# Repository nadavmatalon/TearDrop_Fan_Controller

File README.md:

#TearDrop Fan Controller

##Table of Contents

* [Screenshots](#screenshots)
* [About the Project](#about-the-project)
* [About the Fan Controller](#about-the-fan-controller)
* [License](#license)

##Screenshots

<table>
	<tr>
		<td align="center" width=25% >
			
		</td>
		<td align="center" width=25% >
			
		</td>
		<td align="center" width=25% >
			
		</td>
		<td align="center" width=25% >
			
		</td>
	</tr>
</table>

##About the Project
 
__TearDrop__ is a custom, open-frame, water-cooled scratch build I’ve been 
working on as part of the SnowCrash initiative.

The __SnowCrash__ initiative aims at designing and building end-to-end customized 
personal computers, addressing unique functional requirements – from developing 
the software control applications, to hardware configuration and case modding. 
As part of the initiative's research phase, the TearDrop customized computer 
prototype has been developed.

The underlying motivation for this specifc project was to research, design, 
prototype and finally create everything that's needed for a fully-customized 
desktop computer.

In this context, I’ve learned to program micro-controllers, design, prototype 
and build electronic circuit boards, make CNC cutting templates, interface with 
various kinds of hardware, write front-end applications, and lots more.

This project also helped me to become proficient in multiple software tools, including: 
[Google Sketchup](http://www.sketchup.com/), 
[Arduino IDE](http://www.arduino.cc/), [Processing 2.0](http://processing.org/), 
[CadSoft Eagle](http://www.cadsoftusa.com/download-eagle/freeware/), 
and [Inkscape](http://www.inkscape.org/en/).
 
The __project-log__ of this build (which I haven't had time to update recently, but 
does include loads of cool pictures :-), can be found 
at [bit-tech](http://forums.bit-tech.net/showthread.php?t=234218).

##About the Fan Controller

This repo contains the custom Fan Controller I’ve designed and built 
to control __TearDrop__’s cooling fans.

This repo contains the following files:

* __arduino__

    The source code for the 2 x ATmega328P that run the Fan Controller 

    The files can can be directly accessed by clicking these links:

    * [Fan Controller: IC1](arduino/TearDrop_Fan_Controller_IC1/TearDrop_Fan_Controller_IC1.ino)

    * [Fan Controller: IC2](arduino/TearDrop_Fan_Controller_IC2/TearDrop_Fan_Controller_IC2.ino)

	The source code requires three supporting open-source [Arduino](http://www.arduino.cc/) libraries.

	For convenience, these libraries are inlcuded here in their own sub-folder.

	Credit goes to:

	[PinChangeInt](http://playground.arduino.cc/Main/PinChangeInt)

	[OneWire](https://github.com/ntruchsess/arduino-OneWire/tree/master)

	[WSWire](https://github.com/steamfire/WSWireLib)

* __eagle__

    This folder contains the complete hardware schematics & PCB design of the Fan Controller.

    __Please do not click on the files in this sub-folder as they are in foramts that 
    are incompatible with Github's hosting server__.

    However, the files can be downloaded and run as usual with [CadSoft](http://www.cadsoftusa.com/?language=en)'s 
    free version of [Eagle](http://www.cadsoftusa.com/download-eagle/freeware/).

* __parts__

	A speadsheet with all information about the parts used for building the Fan Controller.

	__The file in this sub-folder is also in a foramt that's incompatible with Github's hosting server__.

    However, it can be downloaded and run as usual with any spreadsheet editing software.

##  License

<p>Released under the <a href="http://www.opensource.org/licenses/MIT">MIT license</a>.</p>

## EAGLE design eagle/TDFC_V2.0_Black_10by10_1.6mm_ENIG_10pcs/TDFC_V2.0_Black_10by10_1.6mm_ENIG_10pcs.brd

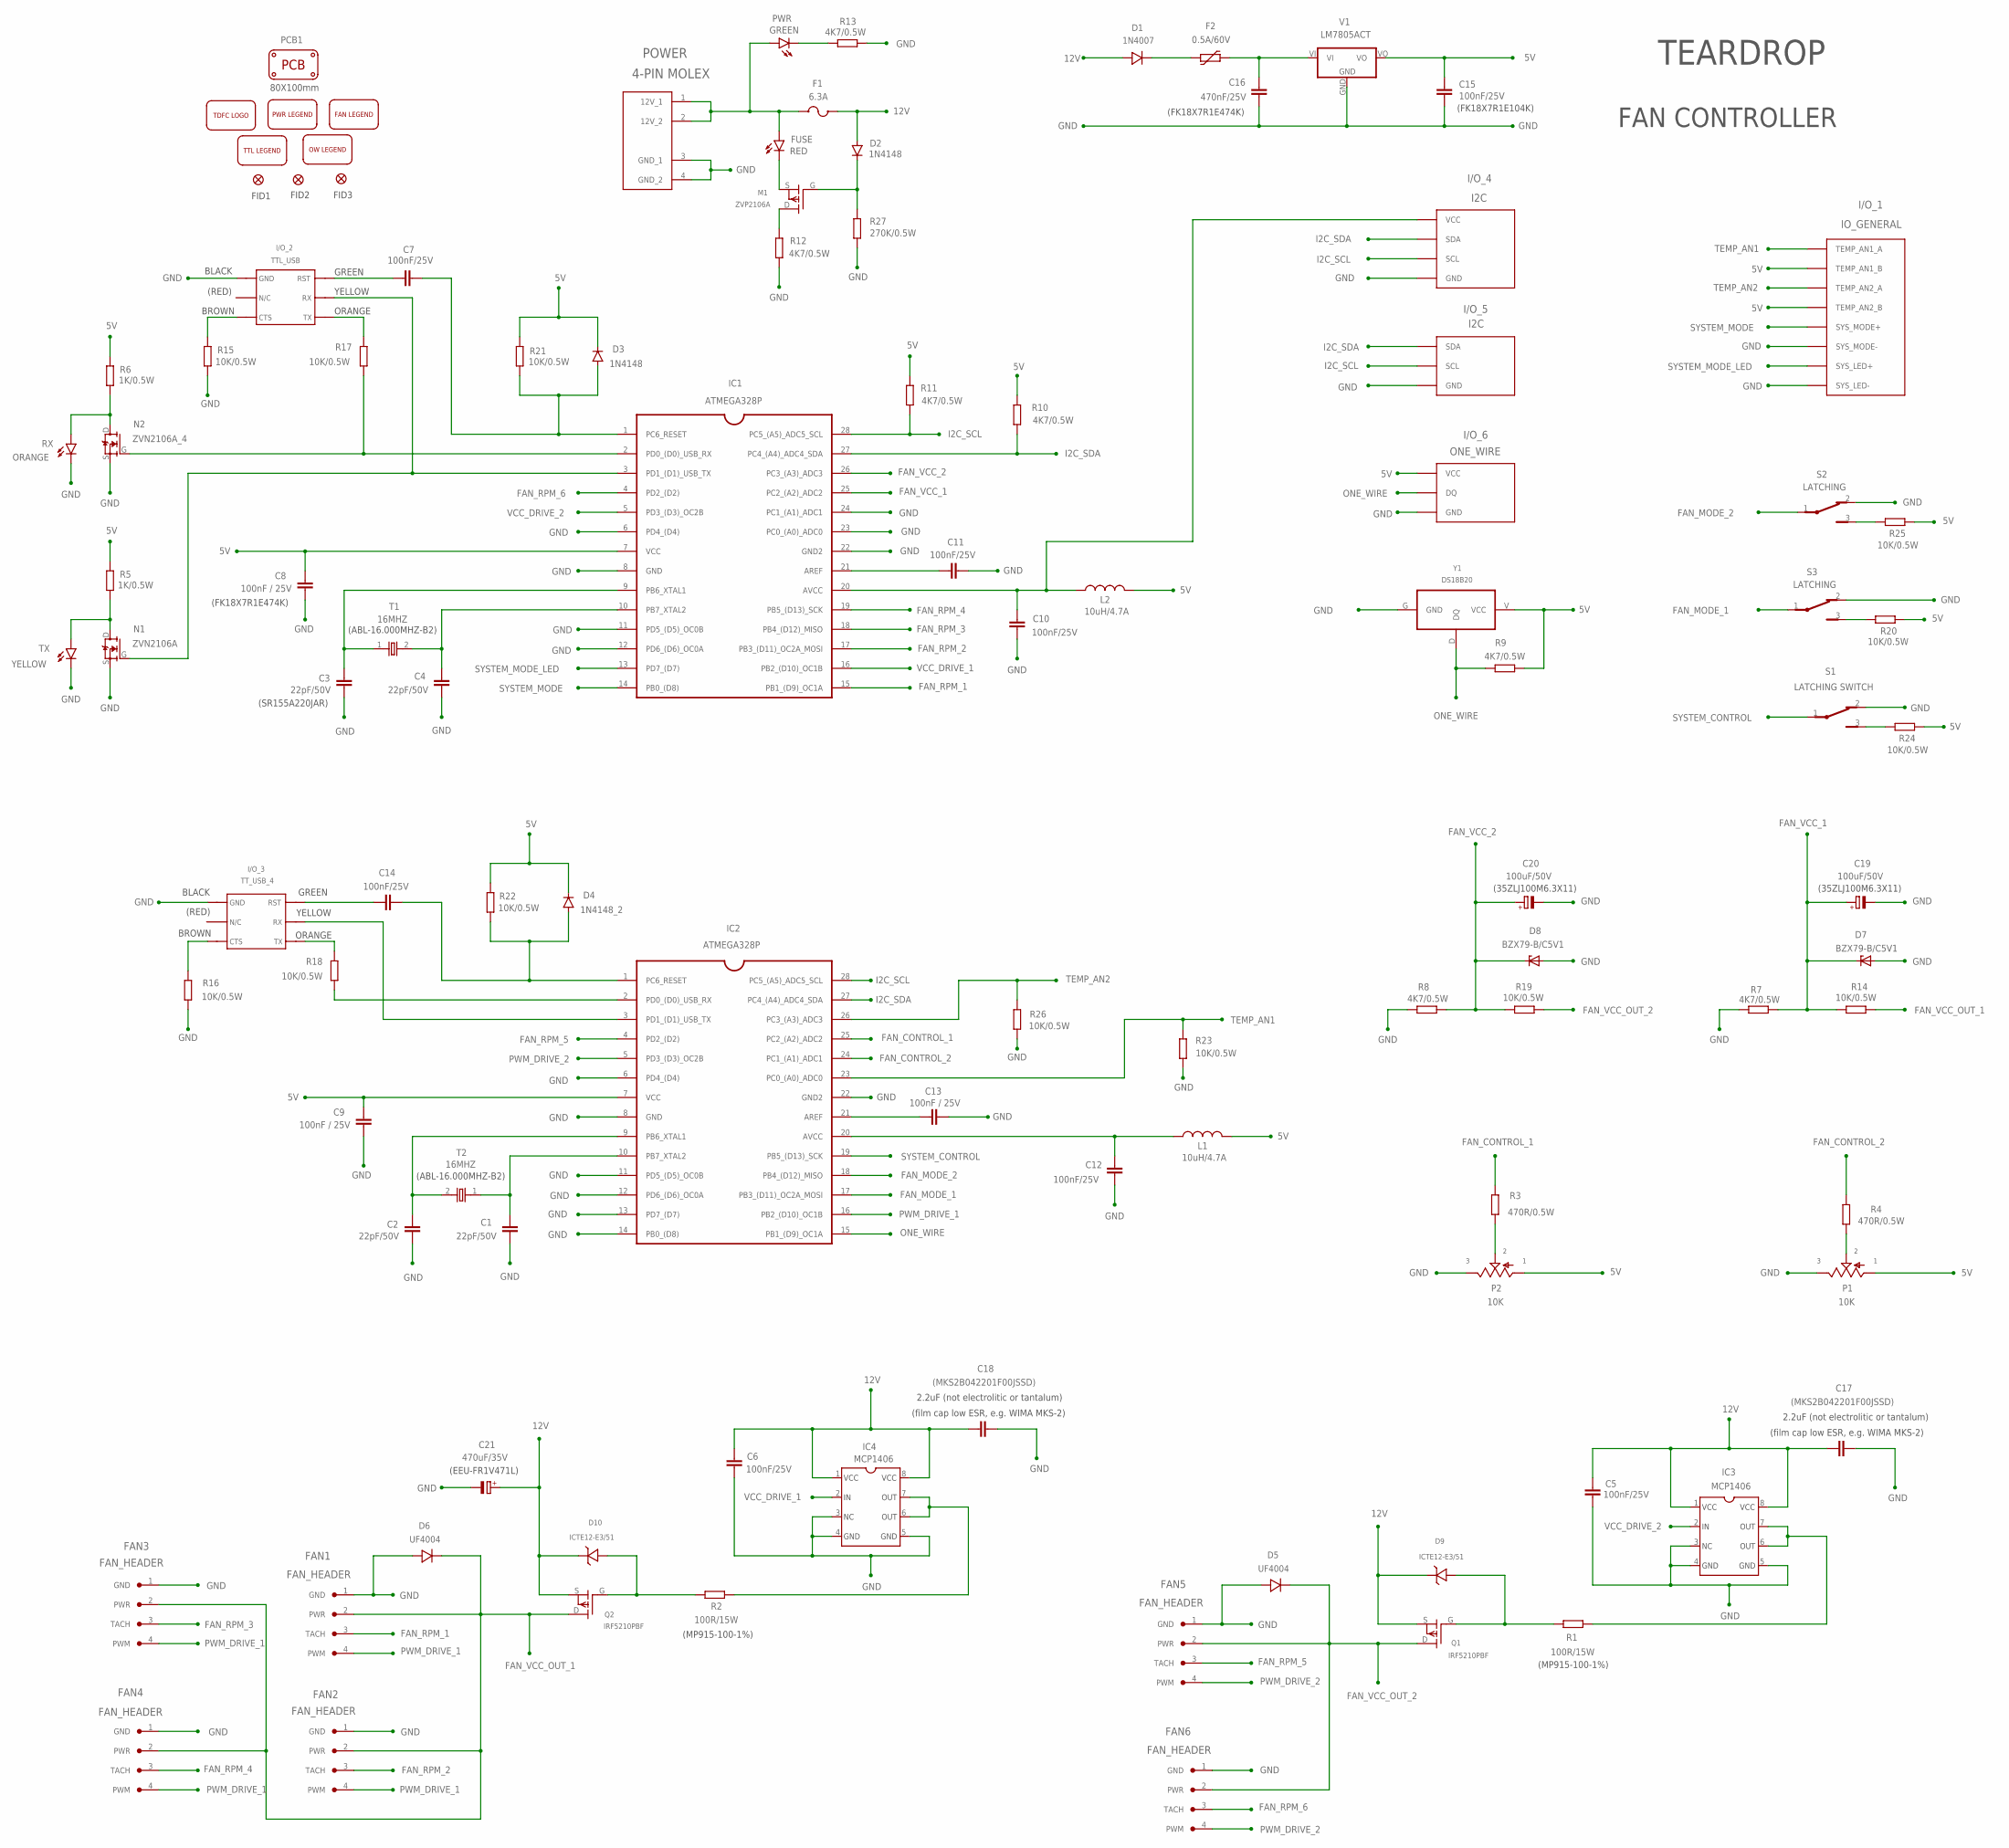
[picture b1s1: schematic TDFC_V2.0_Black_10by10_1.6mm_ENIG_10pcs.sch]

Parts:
C1, C2: 22pF/50V; MLCC_CERAMIC_9
C3, C4: 22pF/50V; MLCC_CERAMIC_11
C5, C6: 100nF/25V; MLCC_CERAMIC_5
C7: 100nF/25V; MLCC_CERAMIC_7
C8, C9: 100nF / 25V; MLCC_CERAMIC_5
C10: 100nF/25V; MLCC_CERAMIC
C11: 100nF/25V; MLCC_CERAMIC_17
C12: 100nF/25V; MLCC_CERAMIC_6
C13: 100nF / 25V; MLCC_CERAMIC_6
C14: 100nF/25V; MLCC_CERAMIC_14
C15: 100nF/25V; MLCC_CERAMIC_16
C16: 470nF/25V; MLCC_CERAMIC_15
C17, C18: (MKS2B042201F00JSSD); WIMA_CAPACITOR_2
C19, C20: 100uF/50V; CAPACITOR_6.3_RIGHT
C21: 470uF/35V; ELECTROLYTIC_CAPACITOR_RIGHT
D1: 1N4007; UF4004
D2, D3: 1N4148
D4: 1N4148_2
D5, D6: UF4004; UF4004_2
D7: BZX79-B/C5V1; DO34_2
D8: BZX79-B/C5V1; DO34Z7
D9, D10: ICTE12-E3/51; TVS_DIODE_5
F1: 6.3A; FUSE_GLASS
F2: 0.5A/60V; PTC
FAN1, FAN2, FAN3, FAN4, FAN5, FAN6: FAN_HEADER; 4PIN_FAN_HEADER
FID1, FID2, FID3: FIDUCIAL1X2; FIDUCIAL-1X2
FUSE: RED; LED_1.8_LEFT
I/O_1: IO_GENERAL; IO_GENERAL_7
I/O_2: TTL_USB; TTL_USB_5
I/O_3: TT_USB_4
I/O_4: I2C; 4_PIN_HEADER_VERTICAL_2
I/O_5: I2C; 3_PIN_VERTICAL_4
I/O_6: ONE_WIRE; 3_PIN_VERTICAL
IC1: ATMEGA328P
IC2: ATMEGA328P; ATMEGA328P_2
IC3, IC4: MCP1406; TC4420
L1, L2: 10uH/4.7A; INDUCTOR
M1: ZVP2106A
N1: ZVN2106A
N2: ZVN2106A_4
P1, P2: 10K; POTENTIMETER_SQUARE
PCB1: 80X100mm; DP10080_V1
POWER: 4-PIN MOLEX; MOLEX_4PIN_2
PWR: GREEN; LED_1.8_LEFT
Q1, Q2: IRF5210PBF; IRF5210
R1, R2: 100R/15W; V234/12
R3, R4: 470R/0.5W; 0204/5
R5, R6: 1K/0.5W; 0204/5
R7, R8, R9, R10, R11, R12, R13: 4K7/0.5W; 0204/5
R14, R15, R16, R17, R18, R19, R20, R21, R22, R23, R24, R25, R26: 10K/0.5W; 0204/5
R27: 270K/0.5W; 0204/5
RX: ORANGE; LED_1.8_LEFT_2
S1: LATCHING SWITCH; SLIDING_SWITCH_4
S2, S3: LATCHING; SLIDING_SWITCH_5
T1, T2: 16MHZ; CRYSTAL_16MHZ
TX: YELLOW; LED_1.8_LEFT_2
U$1: TDFC_LOGO
U$2: MOLEX_4PIN_LEGEND_2
U$3: FAN_HEADER_LEGEND
U$4: TTL_USB_6
U$5: 3_PIN_VERTICAL_LEGEND
V1: LM7805ACT; LM7805
Y1: DS18B20

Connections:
1: C10.1, I/O_4.VCC, IC1.20 (AVCC), L2.1
5V: C8.1, C9.1, C15.2, D3.C, D4.C, I/O_1.TEMP_AN1_B, I/O_1.TEMP_AN2_B, I/O_6.VCC, IC1.7 (VCC), IC2.7 (VCC), L1.2, L2.2, P1.1 (A), P2.1 (A), R5.2, R6.2, R9.2, R10.1, R11.1, R20.1, R21.2, R22.2, R24.2, R25.2, V1.VO, Y1.V (VCC)
12V: C5.2, C6.2, C17.1, C18.1, C21.+, D1.A, D2.A, D9.C, D10.C, F1.2, IC3.1, IC3.8, IC4.1, IC4.8, Q1.S, Q2.S
FAN_CONTROL_1: IC2.25 (PC2_(A2)_ADC2), R3.1
FAN_CONTROL_2: IC2.24 (PC1_(A1)_ADC1), R4.1
FAN_MODE_1: IC2.17 (PB3_(D11)_OC2A_MOSI), S3.1
FAN_MODE_2: IC2.18 (PB4_(D12)_MISO), S2.1
FAN_RPM_1: FAN1.3 (TACH), IC1.15 (PB1_(D9)_OC1A)
FAN_RPM_2: FAN2.3 (TACH), IC1.17 (PB3_(D11)_OC2A_MOSI)
FAN_RPM_3: FAN3.3 (TACH), IC1.18 (PB4_(D12)_MISO)
FAN_RPM_4: FAN4.3 (TACH), IC1.19 (PB5_(D13)_SCK)
FAN_RPM_5: FAN5.3 (TACH), IC2.4 (PD2_(D2))
FAN_RPM_6: FAN6.3 (TACH), IC1.4 (PD2_(D2))
FAN_VCC_1: C19.+, D7.C, IC1.25 (PC2_(A2)_ADC2), R7.1, R14.2
FAN_VCC_2: C20.+, D8.C, IC1.26 (PC3_(A3)_ADC3), R8.1, R19.2
FAN_VCC_OUT_1: D6.C, FAN1.2 (PWR), FAN2.2 (PWR), FAN3.2 (PWR), FAN4.2 (PWR), Q2.D, R14.1
FAN_VCC_OUT_2: D5.C, FAN5.2 (PWR), FAN6.2 (PWR), Q1.D, R19.1
GND: C1.2, C2.2, C3.2, C4.2, C5.1, C6.1, C8.2, C9.2, C10.2, C11.2, C12.2, C13.2, C15.1, C16.2, C17.2, C18.2, C19.-, C20.-, C21.-, D5.A, D6.A, D7.A, D8.A, FAN1.1 (GND), FAN2.1 (GND), FAN3.1 (GND), FAN4.1 (GND), FAN5.1 (GND), FAN6.1 (GND), I/O_1.SYSTEM_LED- (SYS_LED-), I/O_1.SYSTEM_MODE- (SYS_MODE-), I/O_2.GND, I/O_3.GND, I/O_4.GND, I/O_5.GND, I/O_6.GND, IC1.6 (PD4_(D4)), IC1.8 (GND), IC1.11 (PD5_(D5)_OC0B), IC1.12 (PD6_(D6)_OC0A), IC1.22 (GND2), IC1.23 (PC0_(A0)_ADC0), IC1.24 (PC1_(A1)_ADC1), IC2.6 (PD4_(D4)), IC2.8 (GND), IC2.11 (PD5_(D5)_OC0B), IC2.12 (PD6_(D6)_OC0A), IC2.13 (PD7_(D7)), IC2.14 (PB0_(D8)), IC2.22 (GND2), IC3.3, IC3.4, IC3.5, IC4.3, IC4.4, IC4.5, N1.S, N2.S, P1.3 (E), P2.3 (E), POWER.3 (GND_1), POWER.4 (GND_2), R7.2, R8.2, R12.1, R13.1, R15.1, R16.2, R23.2, R26.2, R27.2, RX.K (C), S1.2, S2.2, S3.2, TX.K (C), V1.GND, Y1.G (GND)
I2C_SCL: I/O_4.SCL, I/O_5.SCL, IC1.28 (PC5_(A5)_ADC5_SCL), IC2.28 (PC5_(A5)_ADC5_SCL), R11.2
I2C_SDA: I/O_4.SDA, I/O_5.SDA, IC1.27 (PC4_(A4)_ADC4_SDA), IC2.27 (PC4_(A4)_ADC4_SDA), R10.2
unnamed: C14.1, I/O_3.RST
unnamed: D2.C, M1.G, R27.1
unnamed: C13.1, IC2.21 (AREF)
unnamed: F1.1, FUSE.A, POWER.1 (12V_1), POWER.2 (12V_2), PWR.A
unnamed: PWR.K (C), R13.2
unnamed: I/O_3.RX, IC2.3 (PD1_(D1)_USB_TX)
unnamed: IC3.6, IC3.7, R1.2
unnamed: D10.A, Q2.G, R2.1
unnamed: IC4.6, IC4.7, R2.2
unnamed: FUSE.K (C), M1.S
unnamed: I/O_3.TX, R18.1
unnamed: C11.1, IC1.21 (AREF)
unnamed: D9.A, Q1.G, R1.1
unnamed: I/O_3.CTS, R16.1
unnamed: D1.C, F2.1
unnamed: N1.D, R5.1, TX.A
unnamed: N2.D, R6.1, RX.A
unnamed: M1.D, R12.2
unnamed: R25.1, S2.3
unnamed: C12.1, IC2.20 (AVCC), L1.1
unnamed: R20.2, S3.3
unnamed: IC2.2 (PD0_(D0)_USB_RX), R18.2
unnamed: R24.1, S1.3
unnamed: P2.2 (S), R3.2
unnamed: C4.1, IC1.10 (PB7_XTAL2), T1.2
unnamed: C14.2, D4.A, IC2.1 (PC6_RESET), R22.1
unnamed: C3.1, IC1.9 (PB6_XTAL1), T1.1
unnamed: P1.2 (S), R4.2
unnamed: C2.1, IC2.9 (PB6_XTAL1), T2.2
unnamed: C1.1, IC2.10 (PB7_XTAL2), T2.1
ONE_WIRE: I/O_6.DQ, IC2.15 (PB1_(D9)_OC1A), R9.1, Y1.D (DQ)
POST_FUSE: C16.1, F2.2, V1.VI
PWM_DRIVE_1: FAN1.4 (PWM), FAN2.4 (PWM), FAN3.4 (PWM), FAN4.4 (PWM), IC2.16 (PB2_(D10)_OC1B)
PWM_DRIVE_2: FAN5.4 (PWM), FAN6.4 (PWM), IC2.5 (PD3_(D3)_OC2B)
RESET: C7.1, D3.A, IC1.1 (PC6_RESET), R21.1
SYSTEM_CONTROL: IC2.19 (PB5_(D13)_SCK), S1.1
SYSTEM_MODE: I/O_1.SYSTEM_MODE+ (SYS_MODE+), IC1.14 (PB0_(D8))
SYSTEM_MODE_LED: I/O_1.SYSTEM_LED+ (SYS_LED+), IC1.13 (PD7_(D7))
TEMP_AN1: I/O_1.TEMP_AN1_A, IC2.23 (PC0_(A0)_ADC0), R23.1
TEMP_AN2: I/O_1.TEMP_AN2_A, IC2.26 (PC3_(A3)_ADC3), R26.1
USB_CTS: I/O_2.CTS, R15.2
USB_RESET_2: C7.2, I/O_2.RST
USB_RX: IC1.2 (PD0_(D0)_USB_RX), N2.G, R17.2
USB_RX_2: I/O_2.TX, R17.1
USB_TX: I/O_2.RX, IC1.3 (PD1_(D1)_USB_TX), N1.G
VCC_DRIVE_1: IC1.16 (PB2_(D10)_OC1B), IC4.2
VCC_DRIVE_2: IC1.5 (PD3_(D3)_OC2B), IC3.2

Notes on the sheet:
FID1
FID2
FID3
(film cap low ESR, e.g. WIMA MKS-2)
TEARDROP
GREEN
YELLOW
ORANGE
BROWN
BLACK
(RED)
2.2uF (not electrolitic or tantalum)
(FK18X7R1E104K)
(FK18X7R1E474K)
(SR155A220JAR)
(EEU-FR1V471L)
(35ZLJ100M6.3X11)
(MP915-100-1%)
FAN CONTROLLER
(ABL-16.000MHZ-B2)

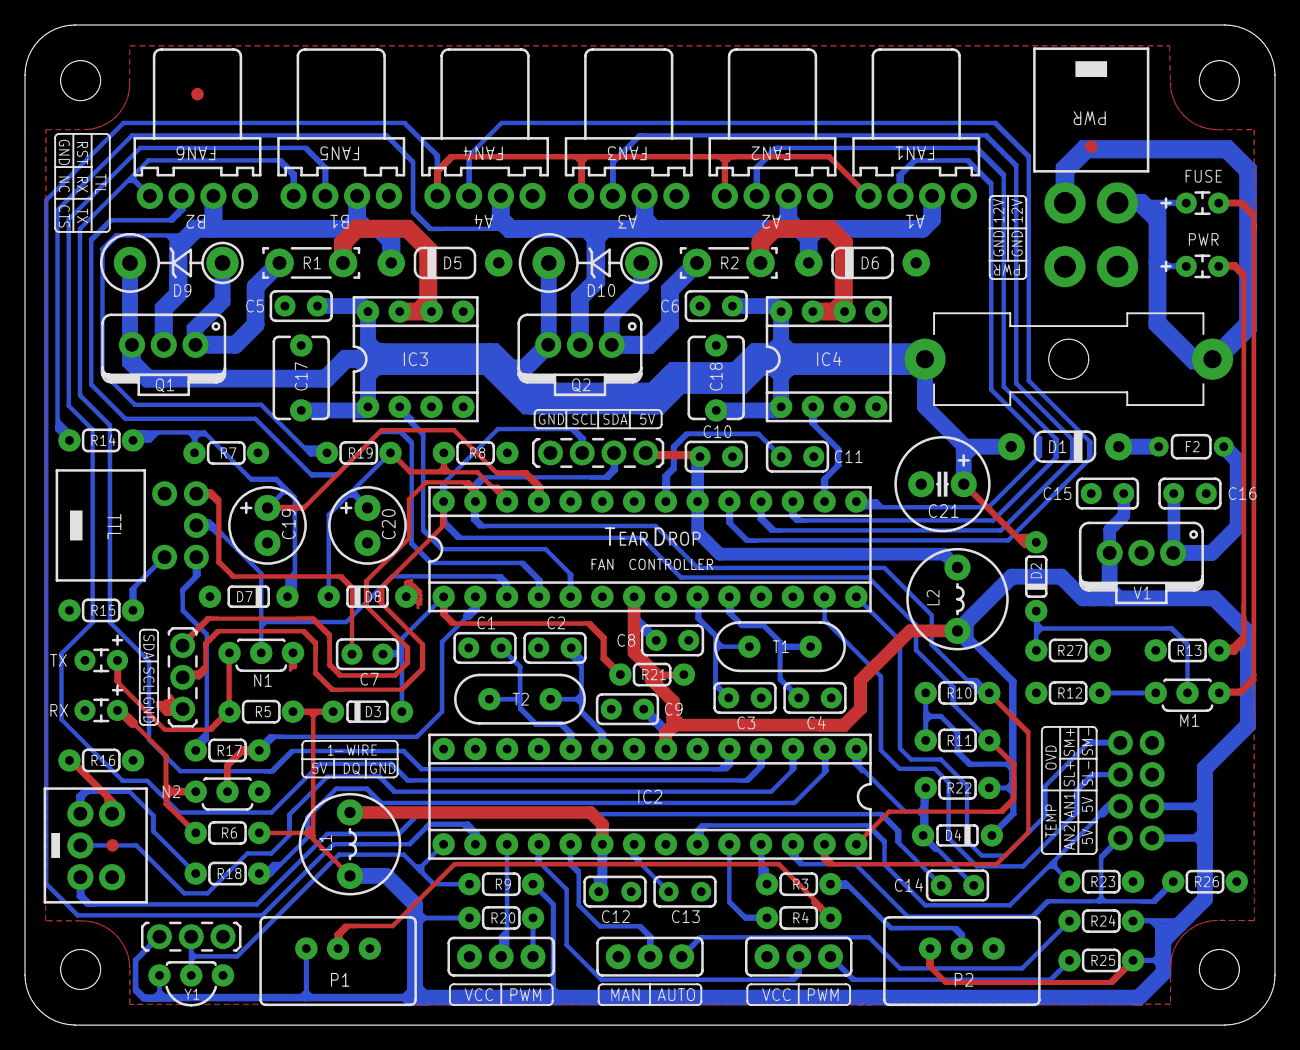
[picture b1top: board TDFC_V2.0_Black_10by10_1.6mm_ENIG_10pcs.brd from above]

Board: 2 copper layers, 100.0 x 80.0 mm, 106 parts (0 on the bottom side), 67 nets.

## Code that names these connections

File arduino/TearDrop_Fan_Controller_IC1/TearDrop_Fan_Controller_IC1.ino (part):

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
// FAN CONTROLLER: IC_1	(COM6)					

// PIN_D2  (PIN 4)  [PD2] - FAN_RPM_6		
// PIN_D3  (PIN 5)  [PD3] - VCC_DRIVE_2 (F_5-6) 
// PIN_D4  (PIN 6)  [PD4] - GND			
// PIN_D5  (PIN 11) [PD5] - GND			
// PIN_D6  (PIN 12) [PD6] - GND			
// PIN_D7  (PIN 13) [PD7] - SYSTEM_CONTROL_LED	
// PIN_D8  (PIN 14) [PB0] - SYSTEM_CONTROL_1 (OVD_ON/OVD_OFF)
// PIN_D9  (PIN 15) [PB1] - FAN_RPM_1
// PIN_D10 (PIN 16) [PB2] - VCC_DRIVE_1 (F_1-4)
// PIN_D11 (PIN 17) [PB3] - FAN_RPM_2
// PIN_D12 (PIN 18) [PB4] - FAN_RPM_3
// PIN_D13 (PIN 19) [PB5] - FAN_RPM_4
// PIN_A0  (PIN 23) [PC0] - GND	
// PIN_A1  (PIN 24) [PC1] - GND
// PIN_A2  (PIN 25) [PC2] - FAN_VCC_1
// PIN_A3  (PIN 26) [PC3] - FAN_VCC_2


// http://playground.arduino.cc/Main/PinChangeInt
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// const boolean PRINT_FOURTH_ROW = true;	// DEBUG_MODE


const byte PIN_D2 = 2;				// FAN_RPM_6	
const byte PIN_D3 = 3;				// VCC_DRIVE_2 (F_5-6) 
const byte PIN_D4 = 4;				// GND
const byte PIN_D5 = 5;				// GND
const byte PIN_D6 = 6;				// GND
const byte PIN_D7 = 7;				// SYSTEM_CONTROL_LED
const byte PIN_D8 = 8;				// SYSTEM_CONTROL_1 (OVD_ON/OVD_OFF)
const byte PIN_D9 = 9;				// FAN_RPM_1
const byte PIN_D10 = 10;			// VCC_DRIVE_1 (F_1-4)
const byte PIN_D11 = 11;			// FAN_RPM_2
const byte PIN_D12 = 12;			// FAN_RPM_3
const byte PIN_D13 = 13;			// FAN_RPM_4
const byte PIN_A0 = A0;				// GND
const byte PIN_A1 = A1;				// GND
const byte PIN_A2 = A2;				// FAN_VCC_1
const byte PIN_A3 = A3;				// FAN_VCC_2

const byte ADC_A0 = 0;										// ADC input channel PIN_A0
const byte ADC_A1 = 1;										// ADC input channel PIN_A1
const byte ADC_A2 = 2;				// FAN_VCC_1					// ADC input channel PIN_A2
const byte ADC_A3 = 3;				// FAN_VCC_2					// ADC input channel PIN_A3
const byte ADC_A4 = 4;										// ADC input channel PIN_A4
const byte ADC_A5 = 5;										// ADC input channel PIN_A5
const byte ADC_TEMP = 8;			// M1_TEMP_IC					// ADC input channel IC_TEMP
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
const unsigned int FC_SYSTEM_CONTROL_1 = 2001;	// SYSTEM_CONTROL_1 (OVD_OFF/OVD_ON)		// FC_SYSTEM_CONTROL_1 processing update command
const unsigned int FC_SYSTEM_CONTROL_2 = 2002;	// SYSTEM_CONTROL_2 (MAN/AUTO)			// FC_SYSTEM_CONTROL_2 processing update command
const unsigned int FC_FAN_VCC_1 = 2003;		// FAN_VCC_1					// FC_FAN_VCC_1 processing update command
const unsigned int FC_FAN_VCC_2 = 2004;		// FAN_VCC_2					// FC_FAN_VCC_2 processing update command
const unsigned int FC_VCC_ICF = 2005;		// VCC_ICF (BOTTOM)				// FC_VCC_IC processing update command
const unsigned int FC_FAN_MODE_1 = 2006;	// FAN_MODE_1 (VCC_1/PWM_1)			// FC_FAN_MODE_1 processing update command
const unsigned int FC_FAN_RPM_1 = 2007;		// FAN_RPM_1					// FC_FAN_RPM_1 processing update command
const unsigned int FC_FAN_RPM_2 = 2008;		// FAN_RPM_2					// FC_FAN_RPM_2 processing update command
const unsigned int FC_FAN_RPM_3 = 2009;		// FAN_RPM_3					// FC_FAN_RPM_3 processing update command
const unsigned int FC_FAN_RPM_4 = 2010;		// FAN_RPM_4					// FC_FAN_RPM_4 processing update command
const unsigned int FC_DUTY_CYCLE_PER_1 = 2011;	// DUTY_CYCLE_PER_1				// FC_DUTY_CYCLE_PER_1 processing update command
const unsigned int FC_FAN_MODE_2 = 2012;	// FAN_MODE_2 (VCC_2/PWM_2)			// FC_FAN_MODE_2 processing update command
const unsigned int FC_FAN_RPM_5 = 2013;		// FAN_RPM_5					// FC_FAN_RPM_5 processing update command
const unsigned int FC_FAN_RPM_6 = 2014;		// FAN_RPM_6					// FC_FAN_RPM_6 processing update command
const unsigned int FC_DUTY_CYCLE_PER_2 = 2015;	// DUTY_CYCLE_PER_2				// FC_DUTY_CYCLE_PER_2 processing update command
const unsigned int FC_TEMP_AN1 = 2016;		// TEMP_AN1					// FC_TEMP_AN3 processing update command
const unsigned int FC_TEMP_AN2 = 2017;		// TEMP_AN2					// FC_TEMP_AN4 processing update command
const unsigned int FC_TEMP_DGF = 2018;		// TEMP_DGF (TEMP_OW_1)				// FC_TEMP_DG processing update command
const unsigned int FC_TEMP_ICF = 2019;		// TEMP_ICF (TOP)				// FC_TEMP_IC processing update command
const unsigned int FC_FREQ_VCC_1 = 2020;	// FREQ_VCC_1					// FC_FREQ_VCC_1 processing update command
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volatile unsigned long ovf1 = 0;		// TIMER1_OVERFLOW				// stores M1_TIMER1 overflow count
volatile unsigned long ovf2 = 0;		// TIMER2_OVERFLOW				// stores M1_TIMER2 overflow count

volatile unsigned long currentBurp_D2 = 0;							// FAN_RPM_6 - stores rpm count for ISR on PIN_D2
volatile unsigned long currentBurp_D9 = 0;							// FAN_RPM_1 - stores rpm count for ISR on PIN_D9
volatile unsigned long currentBurp_D11 = 0;							// FAN_RPM_2 - stores rpm count for ISR on PIN_D11
volatile unsigned long currentBurp_D12 = 0;							// FAN_RPM_3 - stores rpm count for ISR on PIN_D12
volatile unsigned long currentBurp_D13 = 0;							// FAN_RPM_4 - stores rpm count for ISR on PIN_D13

boolean pc_connected = false;			// PC_CONNECTION
boolean check_print = true;
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unsigned int duty_cycle_per_1 = 100;		// DUTY_CYCLE_PER_1				// stores current duty_cycle value as percent (0-100%)
unsigned int duty_cycle_per_2 = 100;		// DUTY_CYCLE_PER_2				// stores current duty_cycle value as percent (0-100%)

unsigned int fan_rpm_1 = 0;			// FAN_RPM_1					// FAN_RPM_1 - stores rpm reading on PIN_D9
unsigned int fan_rpm_2 = 0;			// FAN_RPM_2					// FAN_RPM_2 - stores rpm reading on PIN_D11
unsigned int fan_rpm_3 = 0;			// FAN_RPM_3					// FAN_RPM_3 - stores rpm reading on PIN_D12
unsigned int fan_rpm_4 = 0;			// FAN_RPM_4					// FAN_RPM_4 - stores rpm reading on PIN_D13
unsigned int fan_rpm_5 = 0;			// FAN_RPM_5					// FAN_RPM_5 - stores rpm reading ON IC2
unsigned int fan_rpm_6 = 0;			// FAN_RPM_6					// FAN_RPM_6 - stores rpm reading on PIN_D2

unsigned int temp_AN1 = 0;			// TEMP_AN1					// stores TEMP_AN1 raw data
unsigned int temp_AN2 = 0;			// TEMP_AN2					// stores TEMP_AN2 raw data

unsigned int top_temp_AN = 550;			// TEMP_AN_TOP					// stores the current top temperature between temp_AN1 & temp_AN_2

unsigned int fan_vcc_1 = 0;			// FAN_VCC_1					// stores VCC reading of CHANNEL_1 supply
unsigned int fan_vcc_2 = 0;			// FAN_VCC_2					// stores VCC reading of CHANNEL_2 supply

boolean temp_OW_1_present = false;
boolean temp_OW_2_present = false;
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
void setup() {

	DDRD &= ~(1 << DDD2); PORTD |= (1 << PORTD2);	// FAN_RPM_6 (PIN_D2)			// FAN_RPM_6 - pinMode(PIN_D2, INPUT_PULLUP)
	DDRD |= (1 << DDD3); 				// M1_TIMER2 (PIN_D3)			// VCC_DRIVE_2 (M1_TIMER2) - pinMode(PIN_D3, OUTPUT)
	DDRD &= ~(1 << DDD4);  									// GND - pinMode(PIN_D4, INPUT)
	DDRD &= ~(1 << DDD5);  									// GND - pinMode(PIN_D5, INPUT)
	DDRD &= ~(1 << DDD6);  									// GND - pinMode(PIN_D6, INPUT)
	DDRD |= (1 << DDD7); PORTD &= ~(1 << PORTD7); 	// SYSTEM_CONTROL_LED (PIN_D7)		// SYSTEM_CONTROL_LED - pinMode(PIN_D7, OUTPUT); digitalWrite(PIN_D7, LOW)
	DDRB &= ~(1 << DDB0); PORTB |= (1 << PORTB0);	// SYSTEM_CONTROL_1 (PIN_D8)		// SYSTEM_CONTROL (OVD) - pinMode(PIN_D8, INPUT_PULLUP)
	DDRB &= ~(1 << DDB1); PORTB |= (1 << PORTB1);	// FAN_RPM_1 (PIN_D9)			// FAN_RPM_1 - pinMode(PIN_D9, INPUT_PULLUP)
	DDRB |= (1 << DDB2); 				// M1_TIMER1 (PIN_D10)			// VCC_DRIVE_1 (M1_TIMER1) - pinMode(PIN_D10, OUTPUT)
	DDRB &= ~(1 << DDB3); PORTB |= (1 << PORTB3);	// FAN_RPM_2 (PIN_D11)			// FAN_RPM_2 - pinMode(PIN_D11, INPUT_PULLUP)
	DDRB &= ~(1 << DDB4); PORTB |= (1 << PORTB4);	// FAN_RPM_3 (PIN_D12)			// FAN_RPM_3 - pinMode(PIN_D12, INPUT_PULLUP)
	DDRB &= ~(1 << DDB5); PORTB |= (1 << PORTB5);	// FAN_RPM_4 (PIN_D13)			// FAN_RPM_4 - pinMode(PIN_D13, INPUT_PULLUP)
	DDRC &= ~(1 << DDC0);									// GND - pinMode(PIN_A0, INPUT)
	DDRC &= ~(1 << DDC1);									// GND - pinMode(PIN_A1, INPUT)
	DDRC &= ~(1 << DDC2);				// FAN_VCC_1 (PIN_A2)			// FAN_VCC_1 - pinMode(PIN_A2, INPUT)
	DDRC &= ~(1 << DDC3);				// FAN_VCC_2 (PIN_A3)			// FAN_VCC_2 - pinMode(PIN_A3, INPUT)


// read_ADC() SETUP //
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	Wire.onRequest(request_Call);


	PCintPort::attachInterrupt(PIN_D2, burpCount_D2,FALLING);				// FAN_RPM_6 - attaches software interrupt on PIN_D2
   	PCintPort::attachInterrupt(PIN_D9, burpCount_D9,FALLING);				// FAN_RPM_1 - attaches software interrupt on PIN_D9
  	PCintPort::attachInterrupt(PIN_D11, burpCount_D11,FALLING); 				// FAN_RPM_2 - attaches software interrupt on PIN_D11
   	PCintPort::attachInterrupt(PIN_D12, burpCount_D12,FALLING);				// FAN_RPM_3 - attaches software interrupt on PIN_D12
   	PCintPort::attachInterrupt(PIN_D13, burpCount_D13,FALLING);				// FAN_RPM_4 - attaches software interrupt on PIN_D13


	if (!DEBUG_MODE) {
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
		freq_VCC_1 = update_Frequency(PIN_D10);		// FREQ_VCC_1			// calculates VCC frequency on PIN_D10

		fan_vcc_1 = update_Fan_VCC(PIN_A2);		// FAN_VCC_1			// reads VCC output to CHANNEL1

		freq_VCC_2 = update_Frequency(PIN_D3);		// FREQ_VCC_2			// calculates VCC frequency on PIN_D3

		fan_vcc_2 = update_Fan_VCC(PIN_A3);		// FAN_VCC_2			// reads VCC output to CHANNEL2

		M1_vcc_IC = update_Vcc_IC(); 			// M1_VCC_IC			// reads vcc_IC1

		bottom_vcc_IC = update_Bottom_Vcc_IC();		// VCC_IC_BOTTOM

		fan_rpm_1 = update_Fan_RPM(PIN_D9);		// FAN_RPM_1			// FAN_RPM_1 - updates rpm reading on PIN_D9

		fan_rpm_2 = update_Fan_RPM(PIN_D11);		// FAN_RPM_2			// FAN_RPM_2 - updates rpm reading on PIN_D11
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
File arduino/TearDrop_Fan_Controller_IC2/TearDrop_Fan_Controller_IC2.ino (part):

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
// FAN CONTROLLER: IC_2 (COM4)					

// PIN_D2  (PIN 4)  [PD2] - FAN_RPM_5
// PIN_D3  (PIN 5)  [PD3] - PWM_DRIVE_2 (F_5-6) 
// PIN_D4  (PIN 6)  [PD4] - GND		
// PIN_D5  (PIN 11) [PD5] - GND	
// PIN_D6  (PIN 12) [PD6] - GND	
// PIN_D7  (PIN 13) [PD7] - GND
// PIN_D8  (PIN 14) [PB0] - GND
// PIN_D9  (PIN 15) [PB1] - ONE_WIRE
// PIN_D10 (PIN 16) [PB2] - PWM_DRIVE_1 (F_1-4)
// PIN_D11 (PIN 17) [PB3] - FAN_MODE_1 (VCC_1/PWM_1)
// PIN_D12 (PIN 18) [PB4] - FAN_MODE_2 (VCC_2/PWM_2)
// PIN_D13 (PIN 19) [PB5] - SYSTEM_CONTROL_2 (MAN/AUTO)
// PIN_A0  (PIN 23) [PC0] - TEMP_AN1
// PIN_A1  (PIN 24) [PC1] - FAN_CONTROL_2
// PIN_A2  (PIN 25) [PC2] - FAN_CONTROL_1
// PIN_A3  (PIN 26) [PC3] - TEMP_AN2


// http://playground.arduino.cc/Main/PinChangeInt
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// const boolean PRINT_SECOND_ROW = true;	// DEBUG_MODE


const byte PIN_D2 = 2;				// FAN_RPM_5	
const byte PIN_D3 = 3;				// PWM_DRIVE_2 (F_5-6) 
const byte PIN_D4 = 4;				// GND
const byte PIN_D5 = 5;				// GND
const byte PIN_D6 = 6;				// GND
const byte PIN_D7 = 7;				// GND
const byte PIN_D8 = 8;				// GND
const byte PIN_D9 = 9;				// ONE_WIRE
const byte PIN_D10 = 10;			// PWM_DRIVE_1 (F_1-4)
const byte PIN_D11 = 11;			// FAN_MODE_1 (VCC_1/PWM_1)
const byte PIN_D12 = 12;			// FAN_MODE_2 (VCC_2/PWM_2)
const byte PIN_D13 = 13;			// SYSTEM_CONTROL_2 (MAN/AUTO)
const byte PIN_A0 = A0;				// TEMP_AN1
const byte PIN_A1 = A1;				// FAN_CONTROL_2
const byte PIN_A2 = A2;				// FAN_CONTROL_1
const byte PIN_A3 = A3;				// TEMP_AN2

const byte ADC_A0 = 0;				// TEMP_AN1				// ADC input channel PIN_A0
const byte ADC_A1 = 1;				// FAN_CONTROL_2 (RAW_POT_2)		// ADC input channel PIN_A1
const byte ADC_A2 = 2;				// FAN_CONTROL_1 (RAW_POT_1)		// ADC input channel PIN_A2
const byte ADC_A3 = 3;				// TEMP_AN2				// ADC input channel PIN_A3
const byte ADC_A4 = 4;									// ADC input channel PIN_A4
const byte ADC_A5 = 5;									// ADC input channel PIN_A5
const byte ADC_TEMP = 8;			// M2_TEMP_IC				// ADC input channel IC_TEMP
const byte ADC_VCC = 14;			// M2_VCC_IC				// ADC input channel IC_VCC
const byte ADC_GND = 15;								// ADC input channel IC_GND

const float TEMP_OFFSET_A0 = 1.00;							// TEMP_AN1 - calibration function: higher OFFSET precentage => lower temperature readings
const float TEMP_OFFSET_A3 = 1.00;							// TEMP_AN2 - calibration function: higher OFFSET precentage => lower temperature readings

const unsigned int TEMP_RESISTOR_A0 = 10000;	// TEMP_AN1_RESISTOR			// TEMP_AN1 - resistor value on PIN_A0 (in Ohms)
const unsigned int TEMP_RESISTOR_A3 = 10000;	// TEMP_AN2_RESISTOR			// TEMP_AN2 - resistor value on PIN_A3 (in Ohms)

volatile unsigned long ovf1 = 0;		// TIMER1_OVERFLOW			// stores M2_TIMER1 overflow count
volatile unsigned long ovf2 = 0;		// TIMER2_OVERFLOW			// stores M2_TIMER2 overflow count

volatile unsigned long currentBurp_D2 = 0;						// FAN_RPM_5 - stores rpm count for ISR on PIN_D2

OneWire wireBus(PIN_D9);  						        	// sets up One-Wire bus on PIN_D9

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unsigned int real_pot_1 = 0;			// DEBUG_MODE
unsigned int real_pot_2 = 0;			// DEBUG_MODE

unsigned int fan_rpm_5 = 0;			// FAN_RPM_5				// FAN_RPM_5 - stores rpm reading on ATMEGA328P_2

unsigned int temp_AN1 = 0;			// TEMP_AN1				// stores TEMP_AN1 raw data
unsigned int temp_AN2 = 0;			// TEMP_AN2				// stores TEMP_AN2 raw data

unsigned int top_temp_AN = 550;			// TEMP_AN_TOP

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
void setup() {

	DDRD &= ~(1 << DDD2); PORTD |= (1 << PORTD2);	// FAN_RPM_5 (PIN_D2)		// FAN_RPM_5 - pinMode(PIN_D2, INPUT_PULLUP)
	DDRD |= (1 << DDD3); 				// M2_TIMER2 (PIN_D3)		// PWM_DRIVE_2 (M2_TIMER2) - pinMode(PIN_D3, OUTPUT)
	DDRD &= ~(1 << DDD4);  								// GND - pinMode(PIN_D4, INPUT)
	DDRD &= ~(1 << DDD5);  								// GND - pinMode(PIN_D5, INPUT)
	DDRD &= ~(1 << DDD6);  								// GND - pinMode(PIN_D6, INPUT)
	DDRD &= ~(1 << DDD7);  								// GND - pinMode(PIN_D7, INPUT)
	DDRB &= ~(1 << DDB0);  								// GND - pinMode(PIN_D8, INPUT)
	DDRB |= (1 << DDB2); 				// M2_TIMER1 (PIN_D10)		// PWM_DRIVE_1 (M2_TIMER1) - pinMode(PIN_D10, OUTPUT)
	DDRB &= ~(1 << DDB3); 				// FAN_MODE_1 (PIN_D11)		// FAN_MODE_1 (VCC_1/PWM_1) - pinMode(PIN_D11, INPUT)
	DDRB &= ~(1 << DDB4); 				// FAN_MODE_2 (PIN_D12)		// FAN_MODE_2 (VCC_2/PWM_2) - pinMode(PIN_D12, INPUT)
	DDRB &= ~(1 << DDB5); 				// SYSTEM_CONTROL_2 (PIN_D13)	// SYSTEM_CONTROL_2 (MAN/AUTO) - pinMode(PIN_D13, INPUT)
	DDRC &= ~(1 << DDC0);				// TEMP_AN1			// TEMP_AN1 - pinMode(PIN_A0, INPUT)
	DDRC &= ~(1 << DDC1);				// FAN_CONTROL_2 (RAW_POT)	// FAN_CONTROL_2 - pinMode(PIN_A1, INPUT)
	DDRC &= ~(1 << DDC2);				// FAN_CONTROL_1 (RAW_POT)	// FAN_CONTROL_1 - pinMode(PIN_A2, INPUT)
	DDRC &= ~(1 << DDC3);				// TEMP_AN2			// TEMP_AN2 - pinMode(PIN_A3, INPUT)

// read_ADC() SETUP //

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		TCCR2B |= (1 << CS21);							// turns on Timer2 with prescaler 8
	sei();										// enables global interrupts

	PCintPort::attachInterrupt(PIN_D2, burpCount_D2, FALLING);			// FAN_RPM_5 - attaches software interrupt on PIN_D2


	total_OW_devices = discover_OW_Devices();					// searches & stores total number of temperature sensors on One-Wire bus (max: 4 devices)
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
		system_control_2 = update_Switch(PIN_D13);	// MAN/AUTO

		fan_mode_1 = update_Switch(PIN_D11);		// VCC_1/PWM_1

		fan_mode_2 = update_Switch(PIN_D12);		// VCC_2/PWM_2

		if (!system_control_2) {

			fan_control_1 = update_Fan_Control(PIN_A2);	// FAN_CONTROL_1

			fan_control_2 = update_Fan_Control(PIN_A1);	// FAN_CONTROL_2
		}

		M1_Get_Duty_Data(M1_ADDRESS);			// GET_DUTY_CYCLE	// gets M2_TIMER1 & M2_TIMER2 duty cycle data from M1
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
		vcc_IC = update_Vcc_IC();			// VCC_IC		// reads VCC_IC

		temp_AN1 = update_Temp_AN(PIN_A0);		// TEMP_AN1

		fan_rpm_5 = update_Fan_RPM(PIN_D2);		// FAN_RPM_5		// updates rpm reading on PIN_D2

		temp_AN2 = update_Temp_AN(PIN_A3);		// TEMP_AN2

		top_temp_AN = update_Top_Temp_AN();		// TEMP_AN_TOP

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
		case (PIN_D11):					// VCC_1/PWM_1

			switch_result = bitRead(PINB, 3);							// FAN_MODE_1 (0 => VCC_1; 1 => PWM_1) - digitalRead(PIN_D11)
		
			break;

		case (PIN_D12):					// VCC_2/PWM_2

			switch_result = bitRead(PINB, 4);							// FAN_MODE_2 (0 => VCC_2; 1 => PWM_2) - digitalRead(PIN_D12)

			break;

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
	switch (control_pin) {							

		case (PIN_A2): 					// FAN_CONTROL_1

			current_pot = read_ADC(ADC_A2);
			if (DEBUG_MODE) real_pot_1 = current_pot;
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		        else current_pot = previous_pot_1;
			break;

		case (PIN_A1): 					// FAN_cONTROL_2

			current_pot = read_ADC(ADC_A1);
			if (DEBUG_MODE) real_pot_2 = current_pot;
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	
	switch (temp_pin) {												// sets offset coefficient for selected pin

		case (PIN_A0):						// TEMP_AN1 

			current_an_data = read_ADC(ADC_A0);								// calculates temperature on selected pin

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			break;


		case (PIN_A3): 						// TEMP_AN2

			current_an_data = read_ADC(ADC_A3);								// calculates temperature on selected pin

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
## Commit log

2014-08-25 uploaded TearDrop Fan Controller Files
2014-08-25 updated README file
2014-08-25 added TearDrop images

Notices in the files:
parts and their libraries:
SparkFun-Aesthetics: Licensing: CC v3.0 Share-Alike You are welcome to use this library for commercial purposes.
